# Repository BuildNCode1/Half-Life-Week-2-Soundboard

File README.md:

# Cloudpad - ESP32-C3 Audio Macropad

Cloudpad is a custom-designed, compact 3x3 mechanical macropad featuring an integrated I2S audio amplifier, rotary encoder pitch shifter, metronome, and looping soundboard capabilities.

## Hardware Components
* **MCU:** Seeed Studio XIAO ESP32-C3
* **Audio Amplifier:** Adafruit MAX98357A I2S Class-D Amplifier
* **Speaker:** 3070 Cavity Enclosed Speaker (8Ω / 3W)
* **Inputs:** 3x3 Mechanical Key Matrix + Rotary Encoder with Push-button

## Pin Mapping Reference
* **I2S BCLK:** GPIO 15 (D3)
* **I2S LRC:** GPIO 0 (D0)
* **I2S DIN:** GPIO 16 (D5)
* **Matrix Rows:** GPIO 5, 6, 7
* **Matrix Columns:** GPIO 2, 3, 4
* **Rotary Encoder A/B/Button:** GPIO 8, 9, 10

---

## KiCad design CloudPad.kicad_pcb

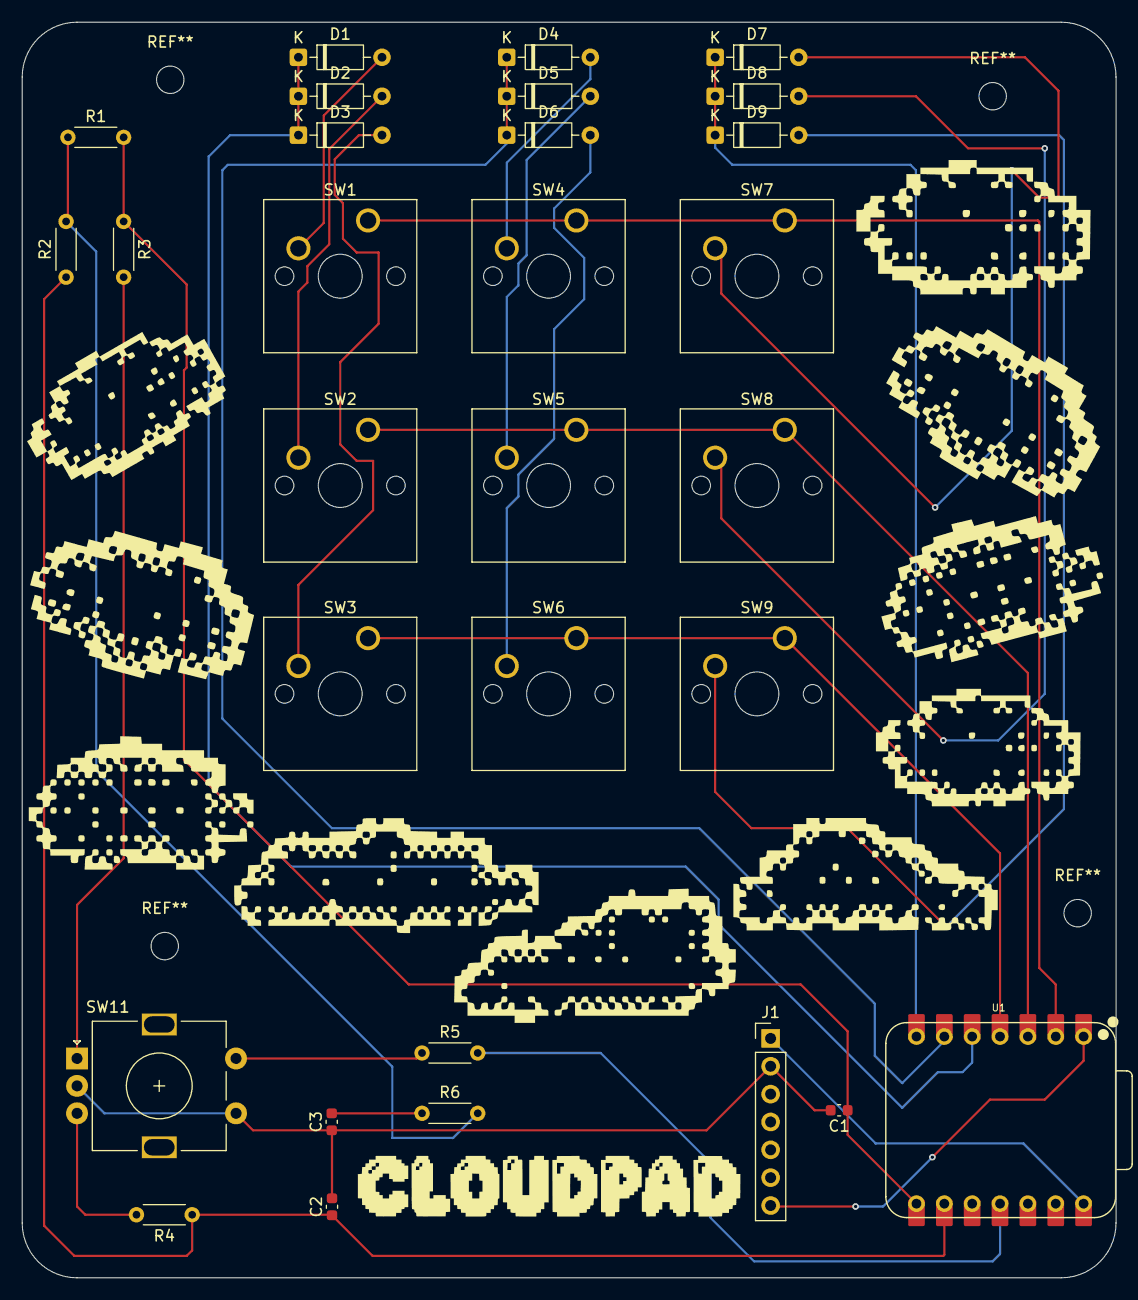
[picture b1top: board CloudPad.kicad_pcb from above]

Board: 2 copper layers, 99.8 x 114.5 mm, 30 parts (0 on the bottom side), 26 nets.

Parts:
C1, C2, C3: u1; C_0603_1608Metric
D1, D2, D3, D4, D5, D6, D7, D8, D9: D; D_DO-35_SOD27_P7.62mm_Horizontal
J1: Conn_01x07; PinHeader_1x07_P2.54mm_Vertical
R1, R2, R6: 10K; R_Axial_DIN0204_L3.6mm_D1.6mm_P5.08mm_Horizontal
R3, R4, R5: k1; R_Axial_DIN0204_L3.6mm_D1.6mm_P5.08mm_Horizontal
SW1, SW2, SW3, SW4, SW5, SW6, SW7, SW8, SW9: SW_Push; SW_Cherry_MX_1.00u_PCB
SW11: RotaryEncoder_Switch; RotaryEncoder_Alps_EC11E-Switch_Vertical_H20mm
U1: XIAO-ESP32-C3-SMD; XIAO-ESP32-C6-DIP

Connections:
+3V3: R1.1, R2.2, R6.2
Col 0: SW1.1, SW4.1, SW7.1, U1.2 (D1)
Col 1: SW2.1, SW5.1, SW8.1, U1.3 (D2)
Col 2: SW3.1, SW6.1, SW9.1, U1.4 (D3)
GND: C1.2, C2.2, C3.1, J1.2, SW11.C, SW11.S1
Lrclk: J1.7, U1.1 (D0)
unnamed: C3.2, R6.1
unnamed: D1.2 (A), SW1.2
unnamed: D2.2 (A), SW2.2
unnamed: D3.2 (A), SW3.2
unnamed: D4.2 (A), SW4.2
unnamed: D5.2 (A), SW5.2
unnamed: D6.2 (A), SW6.2
unnamed: D7.2 (A), SW7.2
unnamed: D8.2 (A), SW8.2
unnamed: D9.2 (A), SW9.2
unnamed: R3.2, SW11.A
unnamed: R4.2, SW11.B
unnamed: R5.1, SW11.S2
ROT1 A: C1.1, R1.2, R3.1, U1.8 (D7)
ROT1 B: C2.1, R2.1, R4.1, U1.9 (D8)
ROT1 S: R5.2, U1.11 (D10)
Row 0: D1.1 (K), D2.1 (K), D3.1 (K), U1.5 (D4)
Row 1: D4.1 (K), D5.1 (K), D6.1 (K), U1.6 (D5)
Row 2: D7.1 (K), D8.1 (K), D9.1 (K), U1.7 (D6)
Vdd: J1.1, U1.14 (VBUS)
